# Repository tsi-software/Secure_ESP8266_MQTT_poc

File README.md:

# Secure ESP8266 MQTT proof of concept
*Copyright (c) 2019 Warren Taylor.*

There are many in depth and well documented ESP8266 MQTT tutorials out there. This in not one of them. This is a brief proof of concept where “security first” is the focus, rather than an afterthought. The goal of this project is to have a documented and working **secure** MQTT Broker and Client, which can be used as a reference for later projects.
If you’re a first timer this project probably isn’t for you.

## Disclaimer
The following documentation in no way guarantees a secure system.
*See [LICENSE](LICENSE).*

## Features
- MQTT Publish/Subscribe Messaging secured using TLS 1.2
- OTA (Over-the-air) Client firmware updates.
- As of this writing esp8266 Secure Encrypted OTA is still in beta.

# Top Level Components
- Secure MQTT Server setup
- Secure ESP8266 MQTT Client
- AVR SPI Slave

# High Level Design 

## Secure MQTT Broker
The MQTT Broker named Mosquitto is installed on the OpenWRT Wifi router. Running the MQTT Broker on the Wifi router is an experiment, which has so far worked just fine. However, the MQTT Broker could be run on any other computer on the same local area network (LAN). You could even run it on a Raspberry PI if performance isn’t a strict requirement.
<br>[MQTT Broker secure setup - detail](top-level-components/mqtt_server_setup#mqtt-broker-secure-setup)

## Secure ESP8266 MQTT Client
Again, there are many tutorials on how to program the ESP8266 as an MQTT Client. But it's hard to find a single source clearly describing how to program the ESP8266 as a **secure** MQTT Client. As a long time software engineer I know how important security is these days.
<br>[Secure ESP8266 MQTT Client - detail](top-level-components/secure_esp8266_mqtt_client#secure-esp8266-mqtt-client)

## AVR SPI Slave
The original plan was to connect peripherals directly to the ESP8266 data pins but I ran out of pins very quickly. Since I had an unused ATmega168 lying around I though “what the heck” and connected the two chips via SPI with the ESP8266 as the master and the ATmega as the slave. In additions to giving me a lot more data pins this scheme also gave me 5v tolerance. I’m also very happy I went this route because it has led to a number of additional useful ideas, which I will come to later.
<br>[AVR SPI Slave - detail](top-level-components/avr_spi_slave#avr-spi-slave)

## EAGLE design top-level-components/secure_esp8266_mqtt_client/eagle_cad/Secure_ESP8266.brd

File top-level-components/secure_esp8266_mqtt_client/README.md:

# Secure ESP8266 MQTT Client
*Copyright (c) 2019-2021 Warren Taylor.*

There are many tutorials on how to program the ESP8266 as an MQTT Client using the Arduino libraries. But it's hard to find a single source clearly describing how to program the ESP8266 as a **secure** MQTT Client. As a long time software engineer I know how important security is these days.

> This project uses the [ESP8266 Arduino Core](https://arduino-esp8266.readthedocs.io/) library and board specifications.

## Disclaimer
The following documentation in no way guarantees a secure system.
*See [LICENSE](../../LICENSE).*

## Security First
At a high level of abstraction secure connections for ESP8266 devices are straight forward when using the arduino-esp8266 **BearSSL::WiFiClientSecure** class.
This is because the **BearSSL::WiFiClientSecure** class extends from the insecure arduino-esp8266 **WiFiClient** class.
What gets complicated is properly initializing a BearSSL::WiFiClientSecure object, which is what this project focuses on.
Once the secure initialization is done the remaining code is implemented mostly the same as the insecure **WiFiClient** class, of which there are many examples.

## ArduinoOTA
The ArduinoOTA library was initially used but later removed from this code because there did not appear to be sufficient resources in the ESP8266 to have a secure connection open by both the MQTT Broker and ArduinoOTA at the same time.
In the future, Secure OTA will be implemented differently in order to coexist with Secure MQTT.

## Source Files

### secure_esp8266_mqtt_client.ino
This is the top level application source code that:
* Connects to the WAP (Wireless Access Point - a.k.a. Wifi Router).
* Securely connects to the MQTT Broker.
* Subscribes to the desired MQTT topics.
* Handles incoming MQTT messages.
* Controls ESP8266 Chip Level Data Pins.
* Configures and manages communications over SPI (Serial Peripheral Interface) to a connected ATmega168. An ATmega168 is used because it has 5V tolerant pins.

### SetupWifi.cpp and SetupWifi.h
This **SetupWifi** class handles the security and encapsulates the arduino-esp8266 **BearSSL::WiFiClientSecure** object.
This class holds the ssid and password of the Wifi Router and implements the code to connect to that router.
This class also holds the ca_cert, client_cert, and client_key used to make secure connections using the **BearSSL::WiFiClientSecure** class.
These certificates and keys were generated when
[Creating the MQTT Keys and Certificates](../mqtt_server_setup#creating-the-mqtt-keys-and-certificates).
Another detail handled by this class, that is not at first obvious, is accurately setting the ESP8266 clock.
This is needed because security certificates can, and should, have an expiry date,
which is very important in order to prevent old and possibly compromised certificates from being reused.
Additionally, UTC (a.k.a. Zulu time) is the internal standard used throughout this project both for consistency
and to avoid potential errors arising from differing time zones and daylight savings time.

### secure_credentials.h
This file contains a copy of the required certificates and keys that were generated when
[Creating the MQTT Keys and Certificates](../mqtt_server_setup#creating-the-mqtt-keys-and-certificates).
> Storing credentials in source code in considered both insecure and bad practice! One of the main reasons for this is because source code that is committed to your revision control system becomes openly accessible (the opposite of secure).
In a subsequent version of this project "secure_credentials.h" will be removed and
replaced with a method of securely injecting credentials into the target devices.

### AsyncWait.h
AsyncWait.h is code that is independent of security but still worth mentioning here.
One of my prime directives is to never write blocking code (code that waits for something to happen but also prevents any other code from executing).
AsyncWait allows me to write code in one place that waits for a duration of time but still allows the main loop() to continue processing.
I think I may write an entirely separate blog on this topic.

### Zones.h
This is application level code, which is independent of security and, therefore, not discussed here.

### globals.h
This is application level code, which is independent of security and, therefore, not discussed here.

### Hardware Schematics

## Arduino Configuration
### Arduino Board Manager
The points here were taken from [arduino-esp8266 readthedocs](https://arduino-esp8266.readthedocs.io/en/latest/installing.html)

* Run **Arduino** and open **Preference**
* Enter *https://arduino.esp8266.com/stable/package_esp8266com_index.json* into Additional Board Manager URLs field.
* Open **Boards Manager**, search for *esp8266*, and install the appropriate board and version. 

### Arduino Library Manager
Open the Arduino Library Manager and install the following libraries:

* PubSubClient by Nick O'Leary

## MQTT Client References
* <https://arduino-esp8266.readthedocs.io/en/latest/esp8266wifi/readme.html>
* <https://arduino-esp8266.readthedocs.io/en/latest/esp8266wifi/bearssl-client-secure-class.html>
* <https://github.com/esp8266/Arduino/blob/master/doc/esp8266wifi/bearssl-client-secure-class.rst>
* <https://github.com/esp8266/Arduino/tree/master/libraries/ESP8266WiFi/examples>
* <https://github.com/esp8266/Arduino/blob/master/libraries/ESP8266WiFi/src/WiFiClientSecureBearSSL.h>
* <https://pubsubclient.knolleary.net/>

## Future Features
### OTA (Over-the-Air) Updates
Future versions of this ESP8266 MQTT Client will have secure OTA updates enabled.
The **ESP8266** will be updated in a manner similar to that of the ArduinoOTA code but instead using the existing secure MQTT connection in order to keep memory use minimal.
The **AVR SPI Slave** will be updated over-the-air by using the ESP8266 as an AVR ISP (In-System Programming) device. Again using the existing secure MQTT connection in order to keep memory use minimal.

# cp210x USB Driver
https://askubuntu.com/questions/941594/installing-cp210x-driver
https://www.silabs.com/products/development-tools/software/usb-to-uart-bridge-vcp-drivers

------
 e.g.
------
$ uname -r
4.9.0-13-amd64

$ uname --all
Linux gonzo 4.9.0-13-amd64 #1 SMP Debian 4.9.228-1 (2020-07-05) x86_64 GNU/Linux

$ lsb_release --all
No LSB modules are available.
Distributor ID: Debian
Description:    Debian GNU/Linux 9.13 (stretch)
Release:        9.13
Codename:       stretch

----------------------------------------
 From the directory containing cp210x.c
----------------------------------------
make
sudo chown root:root cp210x.ko
sudo modprobe --remove --verbose cp210x
sudo cp /lib/modules/"$(uname -r)"/kernel/drivers/usb/serial/cp210x.ko  /lib/modules/"$(uname -r)"/kernel/drivers/usb/serial/cp210x.ko.ORIG1
ls -l /lib/modules/"$(uname -r)"/kernel/drivers/usb/serial
sudo cp cp210x.ko /lib/modules/"$(uname -r)"/kernel/drivers/usb/serial
make clean

cd /lib/modules/"$(uname -r)"/kernel/drivers/usb/serial
#sudo modprobe --verbose usbserial
sudo modprobe --verbose cp210x

sudo dmesg --human --reltime | tail

sudo modinfo usbserial
sudo modinfo cp210x

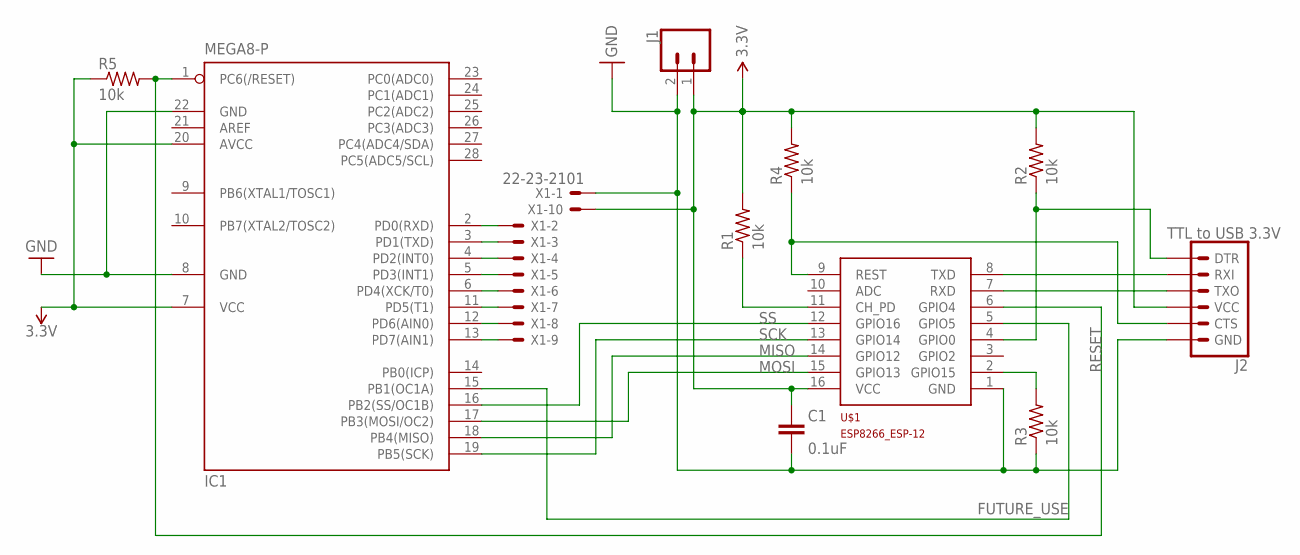
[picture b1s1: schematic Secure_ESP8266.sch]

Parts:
C1: 0.1uF; CAP-PTH-SMALL-KIT
IC1: MEGA8-P; DIL28-3
J1: CONN_02PTH3; 1X02_LONGPADS
J2: TTL to USB 3.3V; 1X06_LONGPADS
R1, R2, R3, R4, R5: 10k; 0204/7
U$1: ESP8266_ESP-12; ESP8266-ESP12
X1: 22-23-2101

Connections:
3.3V: C1.2, IC1.7 (VCC), IC1.20 (AVCC), J1.1, J2.4 (VCC), R1.2, R2.2, R4.2, R5.1, U$1.16 (VCC), X1.10
D0: IC1.2 (PD0(RXD)), X1.2
D1: IC1.3 (PD1(TXD)), X1.3
D2: IC1.4 (PD2(INT0)), X1.4
D3: IC1.5 (PD3(INT1)), X1.5
D4: IC1.6 (PD4(XCK/T0)), X1.6
D5: IC1.11 (PD5(T1)), X1.7
D6: IC1.12 (PD6(AIN0)), X1.8
D7: IC1.13 (PD7(AIN1)), X1.9
FUTURE_USE: IC1.15 (PB1(OC1A)), U$1.5 (GPIO5)
GND: C1.1, IC1.8 (GND), IC1.22 (GND), J1.2, J2.6 (GND), R3.1, U$1.1 (GND), X1.1
MISO: IC1.18 (PB4(MISO)), U$1.14 (GPIO12)
MOSI: IC1.17 (PB3(MOSI/OC2)), U$1.15 (GPIO13)
unnamed: J2.5 (CTS), R4.1, U$1.9 (REST)
unnamed: R1.1, U$1.11 (CH_PD)
unnamed: R3.2, U$1.2 (GPIO15)
unnamed: J2.1 (DTR), R2.1, U$1.4 (GPIO0)
unnamed: J2.2 (RXI), U$1.8 (TXD)
unnamed: J2.3 (TXO), U$1.7 (RXD)
RESET: IC1.1 (PC6(/RESET)), R5.2, U$1.6 (GPIO4)
SCK: IC1.19 (PB5(SCK)), U$1.13 (GPIO14)
SS: IC1.16 (PB2(SS/OC1B)), U$1.12 (GPIO16)

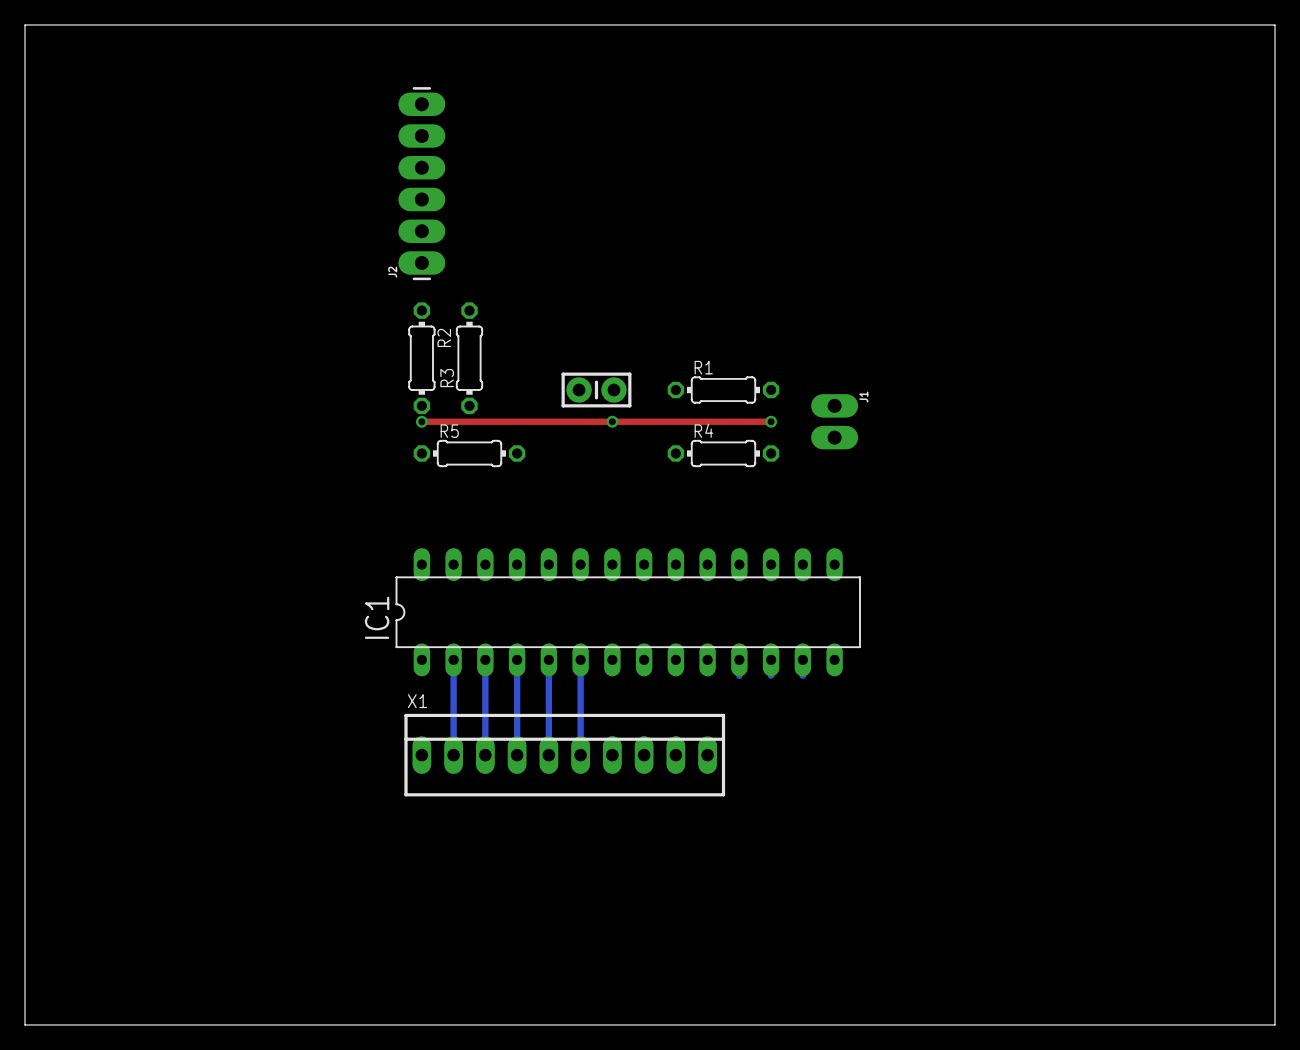
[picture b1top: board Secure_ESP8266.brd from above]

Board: 2 copper layers, 100.0 x 80.0 mm, 11 parts (1 on the bottom side), 22 nets.

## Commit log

2019-01-21 Initial commit.
2019-01-21 A bit of restructuring and documenting.
2019-01-21 Make SetupWifiAndOTA an actual class.
2019-01-22 Successfully implement secure MQTT!
2019-01-22 Remove a source file that was accidentally created.
2019-01-22 Tweak a README.md file.
2019-01-22 Fix a bug: "||" is a short-circuit operator - do not reverse the arguments. Fix a bit of code formatting. Update doc.
2019-01-23 Update some documentation.
2019-01-28 Add code for programResetPin, move value of MQTT_SERVER to secure_credintials.h, and update some docs.
2019-02-02 Work in progress.
2019-02-03 Documentation updates.
2019-02-03 Documentation update.
2019-02-04 Completely remove all references to ArduinoOTA because there does not appear to be sufficient resources in the esp8266 to have a secure connection open to both the MQTT Broker and ArduinoOTA at the s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
2020-06-14 Update to version 0.0.2 and update copyright notices. Use UTC rather than PST timezone.
2021-06-14 Refactor: move UpdateRelays into its own souce files. And revise/update some documentation.
2021-06-23 relay_enclosure.scad - work in progress.
2021-07-12 update README.md, etc...
2023-05-25 Update minor comments and documentation.
2023-09-08 Mosquitto config: allow_anonymous true Update to version 0.0.4 and update copyright notices.
2023-09-12 Clean up client code.

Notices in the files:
parts and their libraries:
SparkFun-Connectors: Licensing: Creative Commons ShareAlike 4.0 International - https://creativecommons.org/licenses/by-sa/4.0
